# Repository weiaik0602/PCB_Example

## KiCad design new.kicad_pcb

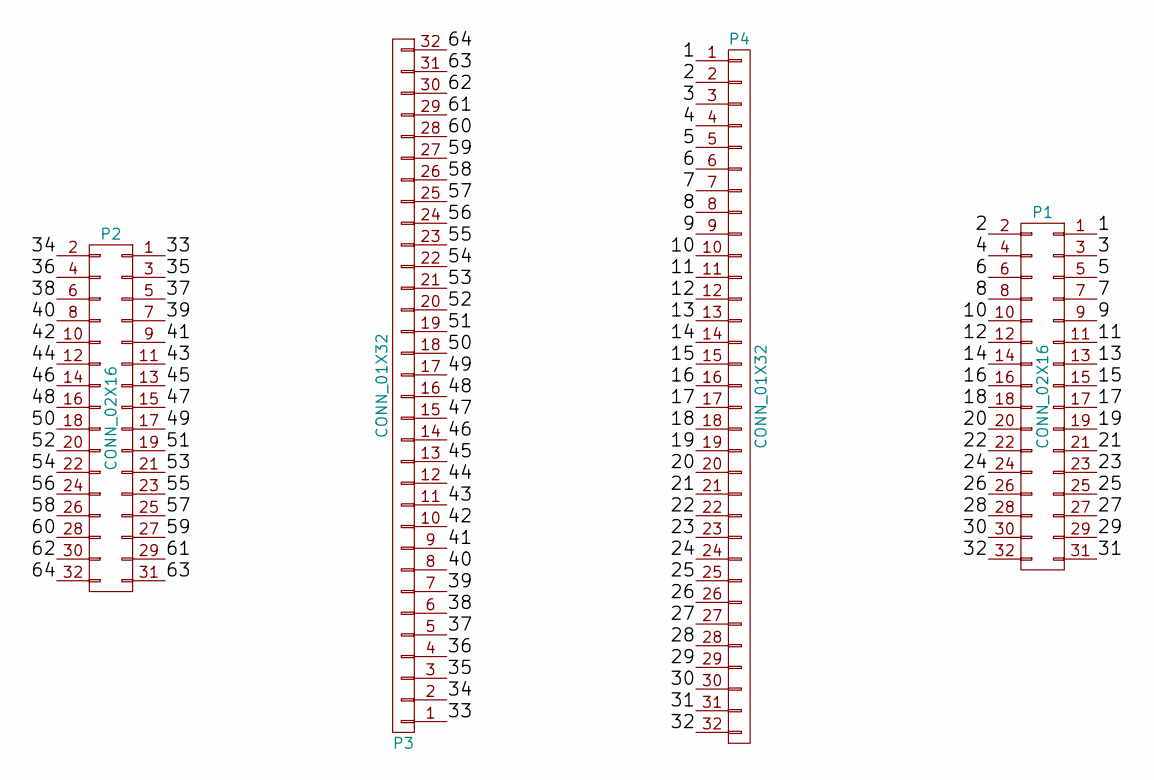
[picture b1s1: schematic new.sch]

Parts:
P1, P2: CONN_02X16; Socket_Strip_Straight_2x16_Pitch2.54mm
P3, P4: CONN_01X32; Pin_Header_Straight_1x32_Pitch2.54mm

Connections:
/1: P1.1, P4.1
/2: P1.2, P4.2
/3: P1.3, P4.3
/4: P1.4, P4.4
/5: P1.5, P4.5
/6: P1.6, P4.6
/7: P1.7, P4.7
/8: P1.8, P4.8
/9: P1.9, P4.9
/10: P1.10, P4.10
/11: P1.11, P4.11
/12: P1.12, P4.12
/13: P1.13, P4.13
/14: P1.14, P4.14
/15: P1.15, P4.15
/16: P1.16, P4.16
/17: P1.17, P4.17
/18: P1.18, P4.18
/19: P1.19, P4.19
/20: P1.20, P4.20
/21: P1.21, P4.21
/22: P1.22, P4.22
/23: P1.23, P4.23
/24: P1.24, P4.24
/25: P1.25, P4.25
/26: P1.26, P4.26
/27: P1.27, P4.27
/28: P1.28, P4.28
/29: P1.29, P4.29
/30: P1.30, P4.30
/31: P1.31, P4.31
/32: P1.32, P4.32
/33: P2.1, P3.1
/34: P2.2, P3.2
/35: P2.3, P3.3
/36: P2.4, P3.4
/37: P2.5, P3.5
/38: P2.6, P3.6
/39: P2.7, P3.7
/40: P2.8, P3.8
/41: P2.9, P3.9
/42: P2.10, P3.10
/43: P2.11, P3.11
/44: P2.12, P3.12
/45: P2.13, P3.13
/46: P2.14, P3.14
/47: P2.15, P3.15
/48: P2.16, P3.16
/49: P2.17, P3.17
/50: P2.18, P3.18
/51: P2.19, P3.19
/52: P2.20, P3.20
/53: P2.21, P3.21
/54: P2.22, P3.22
/55: P2.23, P3.23
/56: P2.24, P3.24
/57: P2.25, P3.25
/58: P2.26, P3.26
/59: P2.27, P3.27
/60: P2.28, P3.28
/61: P2.29, P3.29
/62: P2.30, P3.30
/63: P2.31, P3.31
/64: P2.32, P3.32

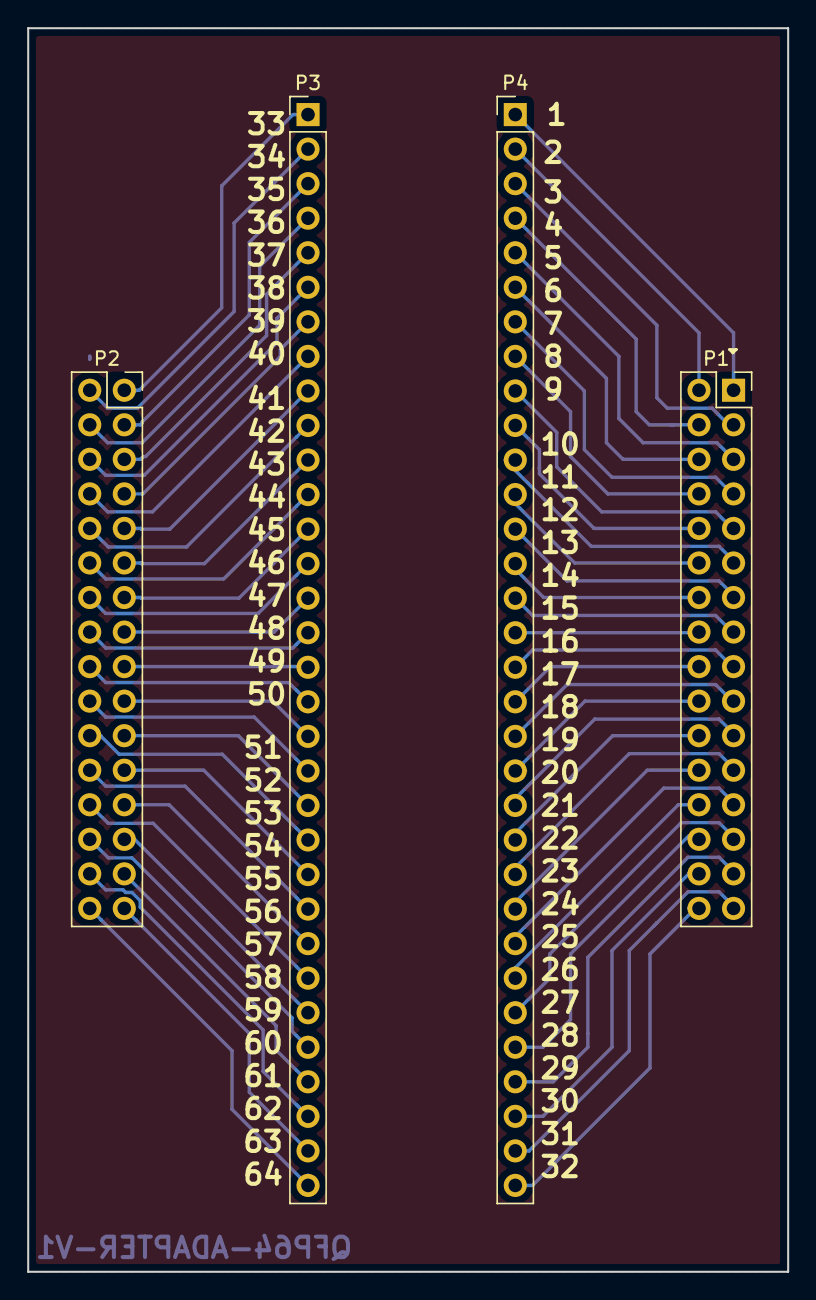
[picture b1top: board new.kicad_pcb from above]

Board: 2 copper layers, 55.9 x 91.4 mm, 4 parts (0 on the bottom side), 64 nets.

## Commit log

2017-10-02 1st commit
2017-10-03 small changes
2017-10-09 changed the pad's shape and added copper pour layer
